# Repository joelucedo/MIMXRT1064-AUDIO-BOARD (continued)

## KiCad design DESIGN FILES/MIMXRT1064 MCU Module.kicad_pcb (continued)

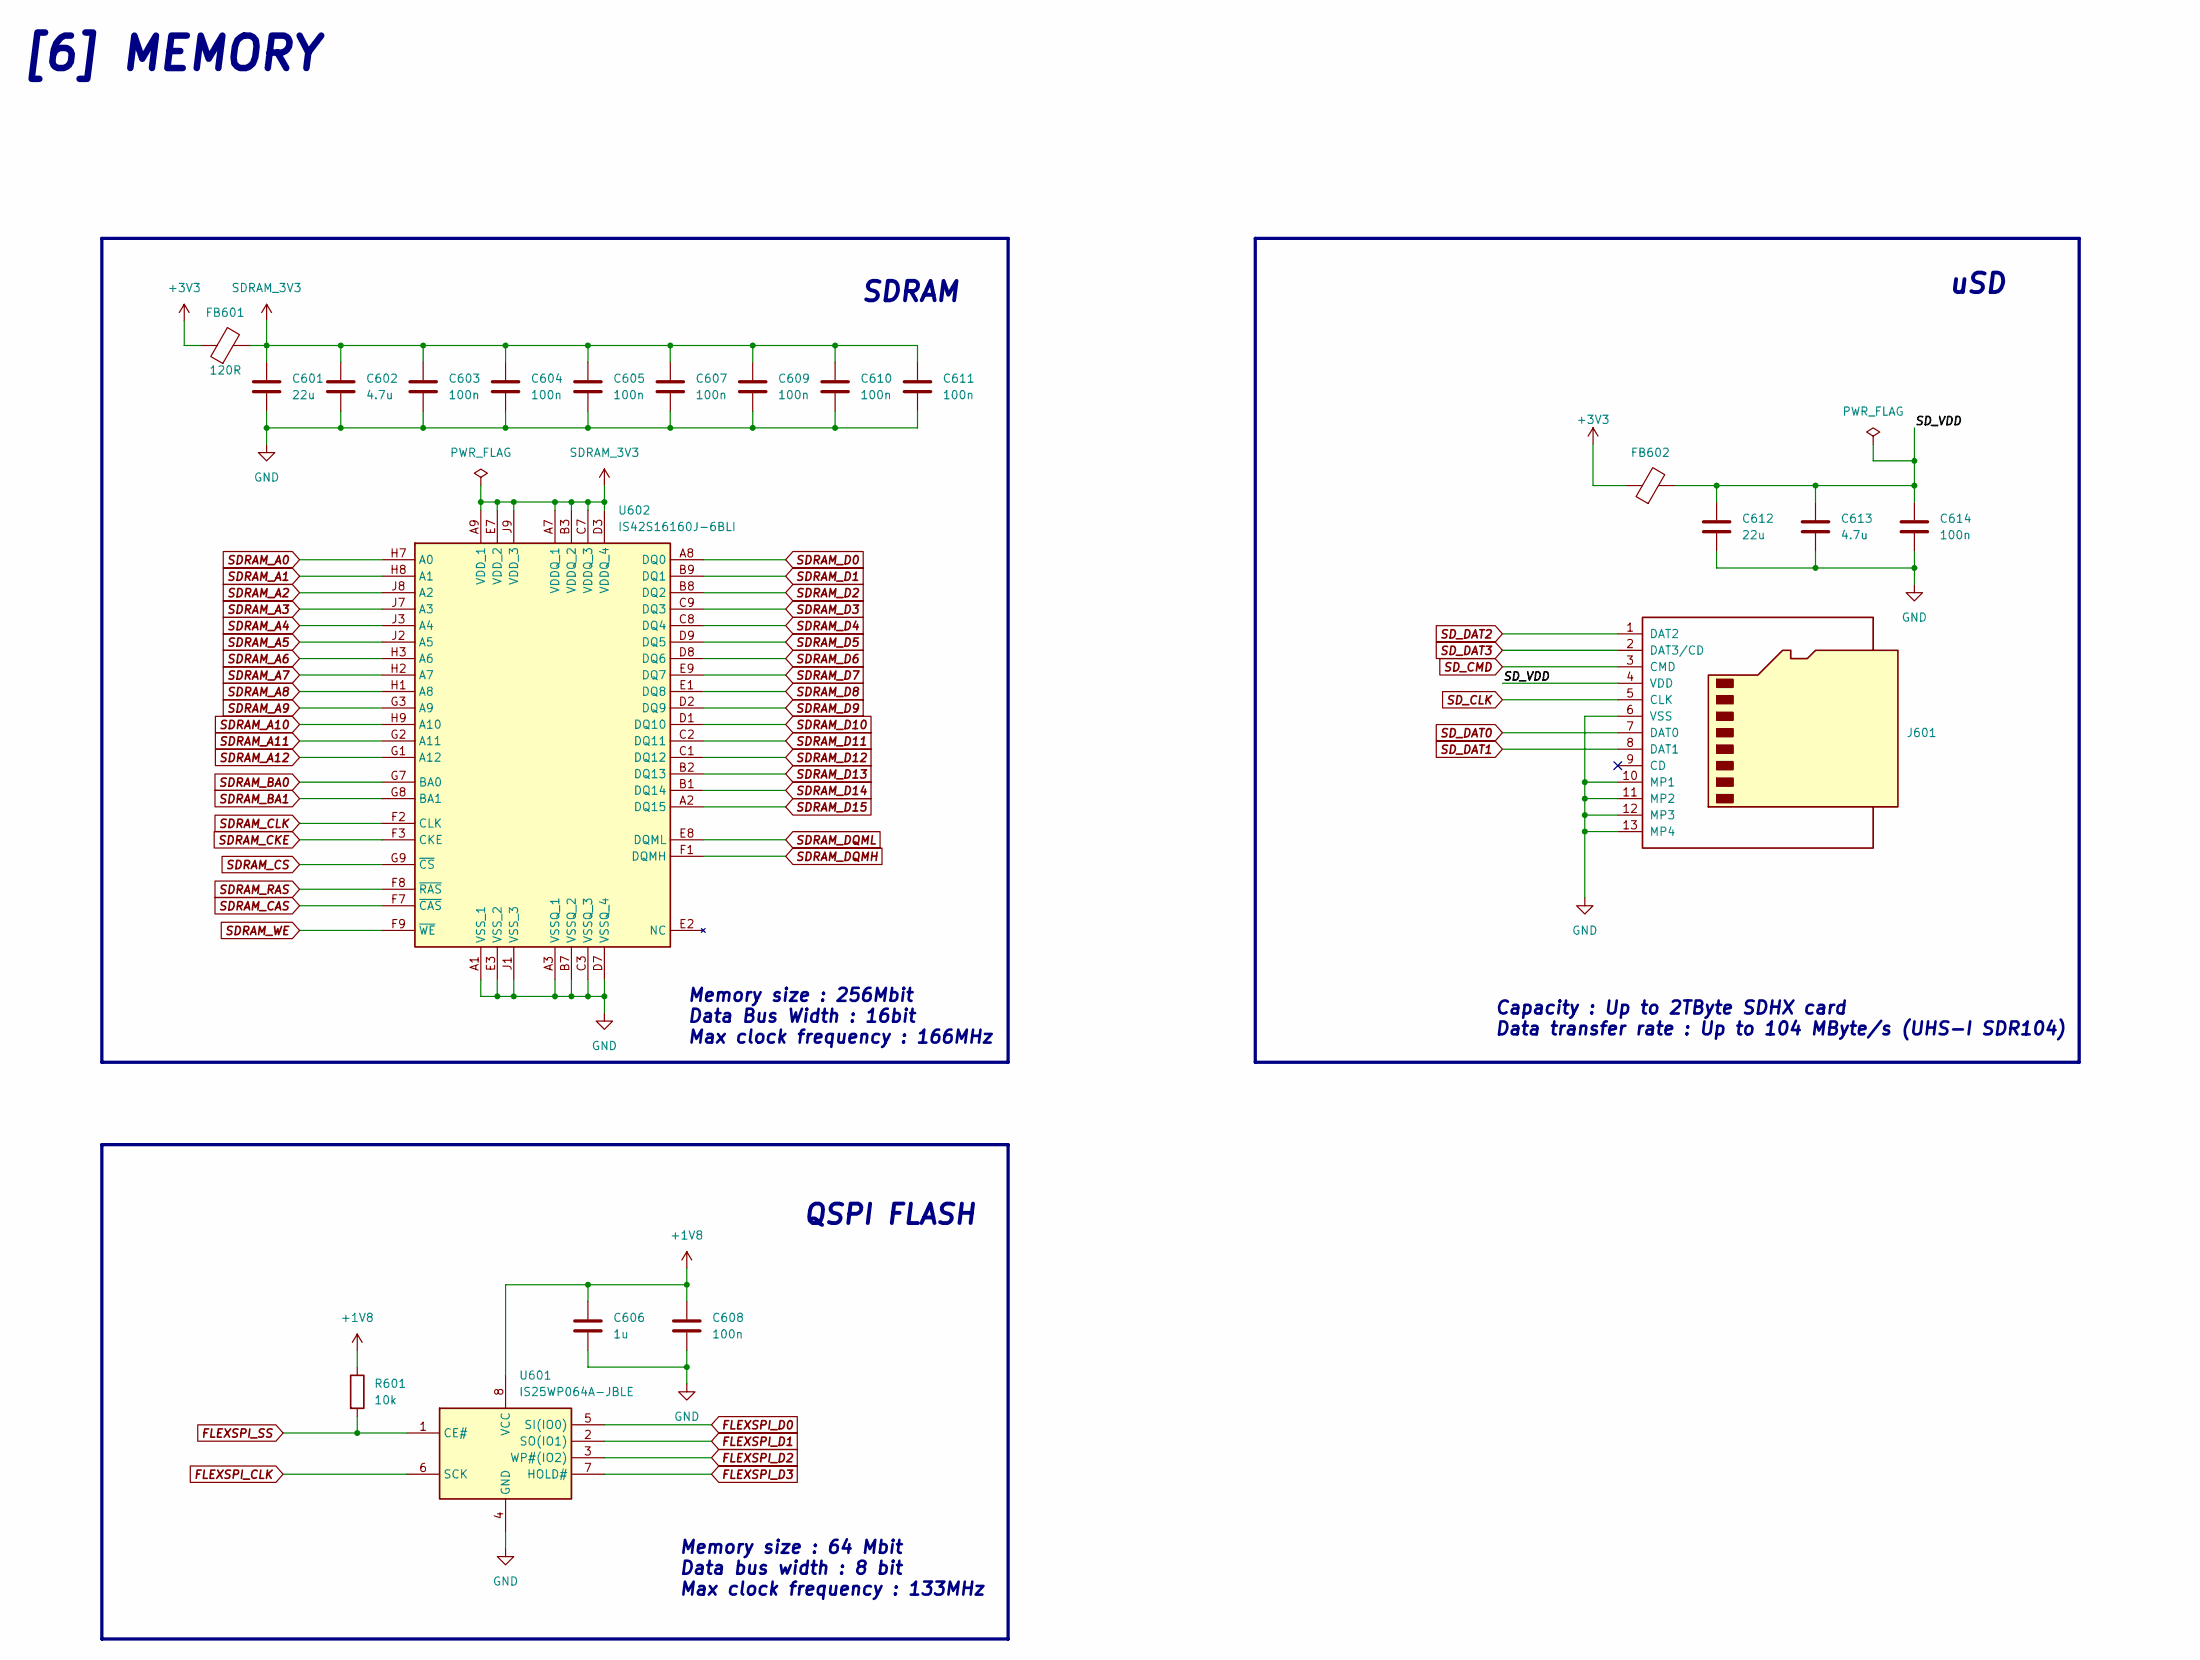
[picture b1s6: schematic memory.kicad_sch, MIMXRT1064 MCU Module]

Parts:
C601, C612: 22u; 0603_CL10A226MQ8NRNC
C602, C613: 4.7u; 0402_CL05A475MP5NRNC
C603, C604, C605, C607, C608, C609, C610, C611, C614: 100n; 0402_CL05B104KB54PNC
C606: 1u; 0402_CL05A105KA5NQNC
FB601: 120R; 0603_BLM18AG121SN1D
FB602: UPZ1608U601-1R3TF; UPZ1608U601-1R3TF_0603
J601: TF-15x15; TF-15x15_smd
R601: 10k; 0402WGF1002TCE
U601: IS25WP064A-JBLE; Manufacturer_Part_Number IS25WP064A-JBLE; Mouser Part Number 870-IS25WP064A-JBLE
U602: IS42S16160J-6BLI; Manufacturer_Part_Number IS42S16160J-6BLI; Mouser Part Number 870-42S16160J6BLI

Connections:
+1V8: C606.1, C608.1, R601.1, U601.8 (VCC); also elsewhere on the board
+3V3: FB601.1, FB602.1; also elsewhere on the board
/MEMORY /SD_VDD: C612.1, C613.1, C614.1, FB602.2, J601.4 (VDD)
FLEXSPI_CLK: U601.6 (SCK); also elsewhere on the board
FLEXSPI_D0: U601.5 (SI(IO0)); also elsewhere on the board
FLEXSPI_D1: U601.2 (SO(IO1)); also elsewhere on the board
FLEXSPI_D2: U601.3 (WP#(IO2)); also elsewhere on the board
FLEXSPI_D3: U601.7 (HOLD#); also elsewhere on the board
FLEXSPI_SS: R601.2, U601.1 (CE#); also elsewhere on the board
GND: C601.2, C602.2, C603.2, C604.2, C605.2, C606.2, C607.2, C608.2, C609.2, C610.2, C611.2, C612.2, C613.2, C614.2, J601.6 (VSS), J601.10 (MP1), J601.11 (MP2), J601.12 (MP3), J601.13 (MP4), U601.4 (GND), U602.A1 (VSS_1), U602.A3 (VSSQ_1), U602.B7 (VSSQ_2), U602.C3 (VSSQ_3), U602.D7 (VSSQ_4), U602.E3 (VSS_2), U602.J1 (VSS_3); also elsewhere on the board
SDRAM_3V3: C601.1, C602.1, C603.1, C604.1, C605.1, C607.1, C609.1, C610.1, C611.1, FB601.2, U602.A7 (VDDQ_1), U602.A9 (VDD_1), U602.B3 (VDDQ_2), U602.C7 (VDDQ_3), U602.D3 (VDDQ_4), U602.E7 (VDD_2), U602.J9 (VDD_3)
SDRAM_A0: U602.H7 (A0); also elsewhere on the board
SDRAM_A1: U602.H8 (A1); also elsewhere on the board
SDRAM_A2: U602.J8 (A2); also elsewhere on the board
SDRAM_A3: U602.J7 (A3); also elsewhere on the board
SDRAM_A4: U602.J3 (A4); also elsewhere on the board
SDRAM_A5: U602.J2 (A5); also elsewhere on the board
SDRAM_A6: U602.H3 (A6); also elsewhere on the board
SDRAM_A7: U602.H2 (A7); also elsewhere on the board
SDRAM_A8: U602.H1 (A8); also elsewhere on the board
SDRAM_A9: U602.G3 (A9); also elsewhere on the board
SDRAM_A10: U602.H9 (A10); also elsewhere on the board
SDRAM_A11: U602.G2 (A11); also elsewhere on the board
SDRAM_A12: U602.G1 (A12); also elsewhere on the board
SDRAM_BA0: U602.G7 (BA0); also elsewhere on the board
SDRAM_BA1: U602.G8 (BA1); also elsewhere on the board
SDRAM_CAS: U602.F7 (~CAS); also elsewhere on the board
SDRAM_CKE: U602.F3 (CKE); also elsewhere on the board
SDRAM_CLK: U602.F2 (CLK); also elsewhere on the board
SDRAM_CS: U602.G9 (~CS); also elsewhere on the board
SDRAM_D0: U602.A8 (DQ0); also elsewhere on the board
SDRAM_D1: U602.B9 (DQ1); also elsewhere on the board
SDRAM_D2: U602.B8 (DQ2); also elsewhere on the board
SDRAM_D3: U602.C9 (DQ3); also elsewhere on the board
SDRAM_D4: U602.C8 (DQ4); also elsewhere on the board
SDRAM_D5: U602.D9 (DQ5); also elsewhere on the board
SDRAM_D6: U602.D8 (DQ6); also elsewhere on the board
SDRAM_D7: U602.E9 (DQ7); also elsewhere on the board
SDRAM_D8: U602.E1 (DQ8); also elsewhere on the board
SDRAM_D9: U602.D2 (DQ9); also elsewhere on the board
SDRAM_D10: U602.D1 (DQ10); also elsewhere on the board
SDRAM_D11: U602.C2 (DQ11); also elsewhere on the board
SDRAM_D12: U602.C1 (DQ12); also elsewhere on the board
SDRAM_D13: U602.B2 (DQ13); also elsewhere on the board
SDRAM_D14: U602.B1 (DQ14); also elsewhere on the board
SDRAM_D15: U602.A2 (DQ15); also elsewhere on the board
SDRAM_DQMH: U602.F1 (DQMH); also elsewhere on the board
SDRAM_DQML: U602.E8 (DQML); also elsewhere on the board
SDRAM_RAS: U602.F8 (~RAS); also elsewhere on the board
SDRAM_WE: U602.F9 (~WE); also elsewhere on the board
SD_CLK: J601.5 (CLK); also elsewhere on the board
SD_CMD: J601.3 (CMD); also elsewhere on the board
SD_DAT0: J601.7 (DAT0); also elsewhere on the board
SD_DAT1: J601.8 (DAT1); also elsewhere on the board
SD_DAT2: J601.1 (DAT2); also elsewhere on the board
SD_DAT3: J601.2 (DAT3/CD); also elsewhere on the board

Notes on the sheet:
QSPI FLASH
Capacity : Up to 2TByte SDHX card Data transfer rate : Up to 104 MByte/s (UHS-I SDR104)
[6] MEMORY
SDRAM
uSD
Memory size : 256Mbit Data Bus Width : 16bit Max clock frequency : 166MHz
Memory size : 64 Mbit Data bus width : 8 bit Max clock frequency : 133MHz

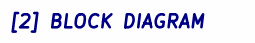
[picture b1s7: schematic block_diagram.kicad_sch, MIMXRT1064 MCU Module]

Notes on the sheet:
[2] BLOCK DIAGRAM

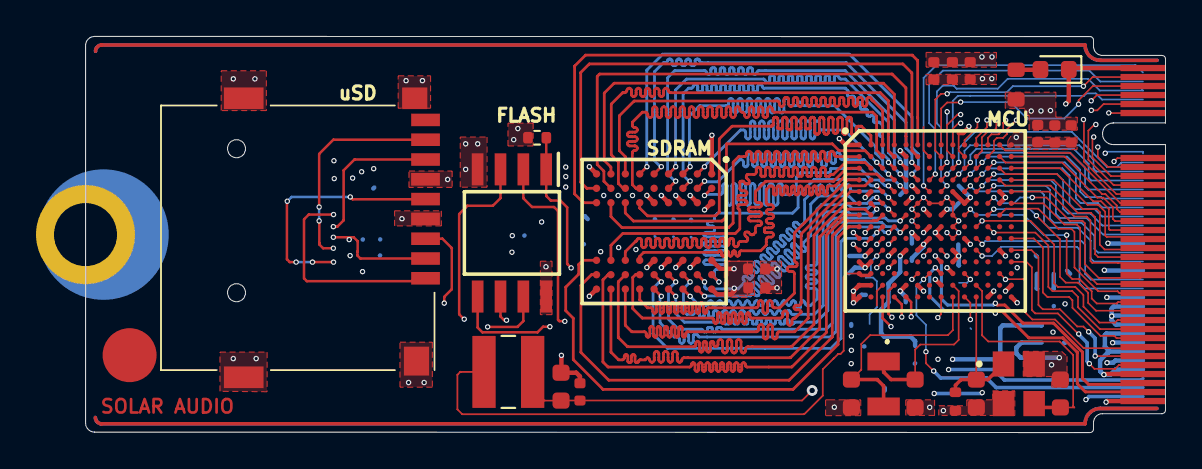
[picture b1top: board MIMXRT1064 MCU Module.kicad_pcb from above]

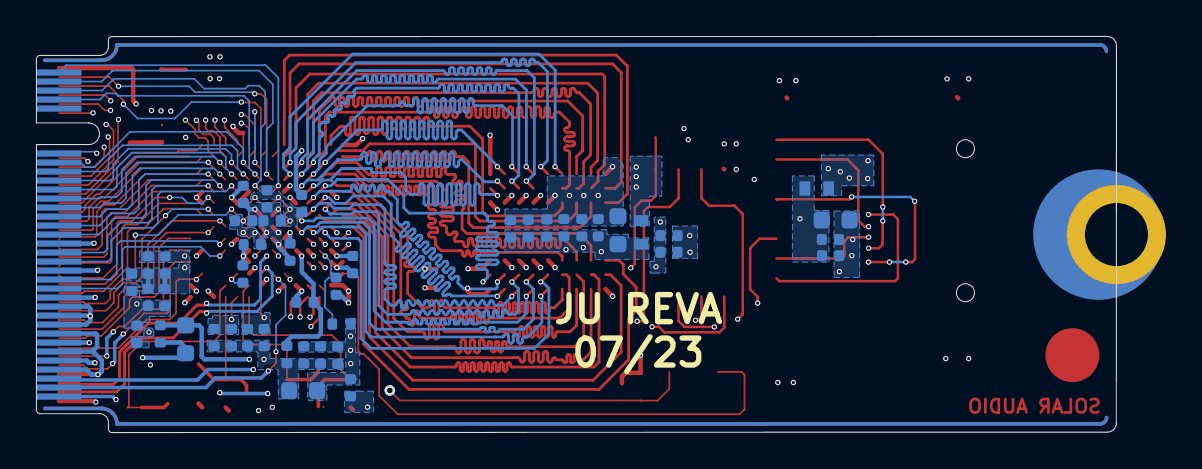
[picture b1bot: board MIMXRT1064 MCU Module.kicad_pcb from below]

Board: 6 copper layers, 60.0 x 22.0 mm, 70 parts (44 on the bottom side), 120 nets.

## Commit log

2023-05-18 Adding project files
2023-05-18 Adding voltage monitor and manual reset circuit
2023-05-18 Refactoring schematic
2023-05-18 vcc check
2023-05-18 Adding BOM and check sheets
2023-05-18 Adding component to BOM
2023-05-18 schematic and lib edit
2023-05-18 work
2023-05-18 footprint checks
2023-05-18 edits
2023-05-19 adding cells
2023-05-19 edit
2023-05-20 adding datasheet
2023-05-20 Adding MPIT4030-680M-LF inductor to BOM
2023-05-20 Adding TLV62569DBVR to BOM
2023-05-20 Adding MPIT4030-680M-LF and TLV62569DBVR to check sheet
2023-05-20 Removing Sylergy DCDC from sheets
2023-05-20 removing SY8089AAAC from library
2023-05-20 symbol check MPIT4030-680M-LF
2023-05-20 TLV62569DBVR symbol check
2023-05-20 Removing audio codec from project
2023-05-20 Adding power on led
2023-05-20 schematic edit
2023-05-20 crystals edit
2023-05-22 schematic changes
2023-05-23 sch changes
2023-05-23 footprints and symbols check
2023-05-23 Deleting datasheet
2023-05-23 changes and adding schematic pdf
